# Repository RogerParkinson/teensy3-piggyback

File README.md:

# teensy3-piggyback
Piggyback board for a Teensy 3 that holds a MicroSD and a LIPO charger
The LIPO charger needs the connector pads on the Teensy opened to run off battery
The switch allows you to switch from battery supply to USB supply or (central position) off.
The LED shows if it is charging or not.
Pin 14/AO can be queried for a current battery voltage. It is not accurate but it is to scale.
The button on the Teensy is covered by the piggy back board, unless you mount it underneath instead of on top. So the button is replicated on the piggy back.
Developed for Teensy 3.0 but the pins on later Teensys look compatible.
Be aware than the pins on the end opposite the USB are not breadboard friendly (like the pins on the Tennsy). If you solder them in place you won't be able to plug into a breadboard unless you trim the ends of those pins down so they don't plug into your breadboard. The side pins can remain as they are and they will work fine with your breadboard.

<a href="https://www.oshpark.com/shared_projects/XkRxbt6A"></img></a>

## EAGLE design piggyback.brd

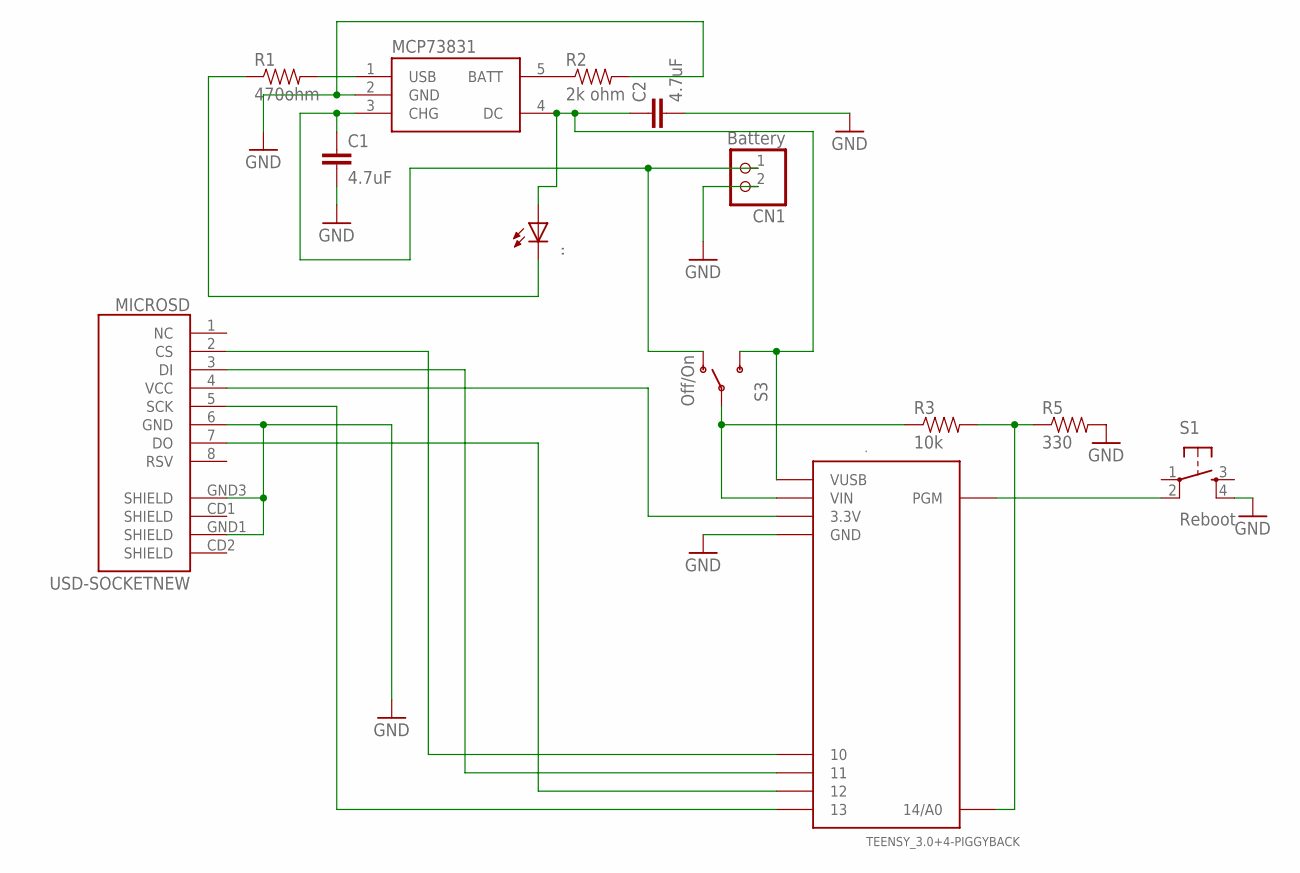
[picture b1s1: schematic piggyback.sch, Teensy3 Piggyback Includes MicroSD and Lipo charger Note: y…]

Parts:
.: TEENSY_3.0+4-PIGGYBACK
..: LEDCHIP-LED0805; CHIP-LED0805
C1, C2: 4.7uF; 0805
CN1: Battery; JST-PH-2-THM
MCP73831: MAX1555; SOT23-5
MICROSD: USD-SOCKETNEW; MICRO-SD-SOCKET-PP
R1: 470ohm; 0805
R2: 2k ohm; 0805
R3: 10k; 0805
R5: 330; 0805
S1: Reboot; TACTILE_SWITCH_SMD
S3: Off/On; SWITCH-SPST-SMD-A

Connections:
DI: ..11, MICROSD.3 (DI)
DO: ..12, MICROSD.7 (DO)
GND: ..GND1 (GND), C1.2, C2.2, CN1.2 (1), MCP73831.2 (GND), MICROSD.6 (GND), MICROSD.GND1 (SHIELD), MICROSD.GND3 (SHIELD), R2.2, R5.2, S1.4
unnamed: MCP73831.5 (BATT), R2.1
unnamed: C1.1, CN1.1 (2), MCP73831.3 (CHG), S3.1 (O)
unnamed 5: ...C, R1.1; also elsewhere on the board
unnamed: MCP73831.1 (USB), R1.2
unnamed 7: ..VUSB, ...A, C2.1, MCP73831.4 (DC), S3.3 (S); also elsewhere on the board
unnamed: ..PGM, S1.2
unnamed: ..VIN, R3.1, S3.2
unnamed: ..3.3V1 (3.3V), MICROSD.4 (VCC)
unnamed: ..14/A0, R3.2, R5.1
unnamed: ..13, MICROSD.5 (SCK)
unnamed: ..10, MICROSD.2 (CS)

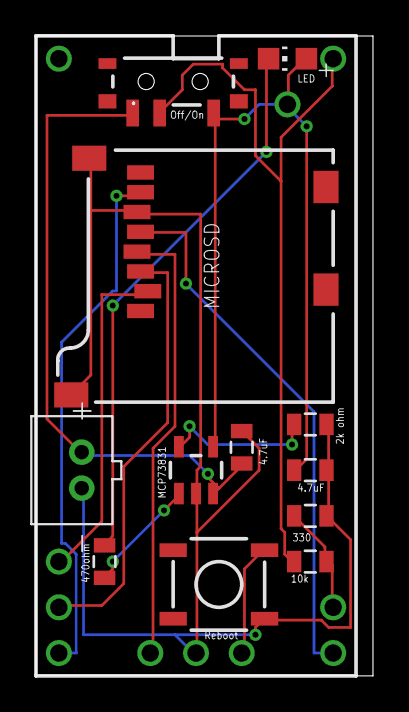
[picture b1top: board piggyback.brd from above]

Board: 2 copper layers, 18.7 x 35.5 mm, 13 parts (0 on the bottom side), 14 nets.

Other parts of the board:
LED: LED; CHIP-LED0805

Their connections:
unnamed 5: LED.C; also elsewhere on the board
unnamed 7: LED.A; also elsewhere on the board

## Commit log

2016-05-29 Fixed some missing component values
2016-05-29 Small change to ReadMe

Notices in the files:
piggyback.brd:
(c)2014 Roger Parkinson
parts and their libraries:
SparkFun-Electromechanical: Licensing: CC v3.0 Share-Alike You are welcome to use this library for commercial purposes.
